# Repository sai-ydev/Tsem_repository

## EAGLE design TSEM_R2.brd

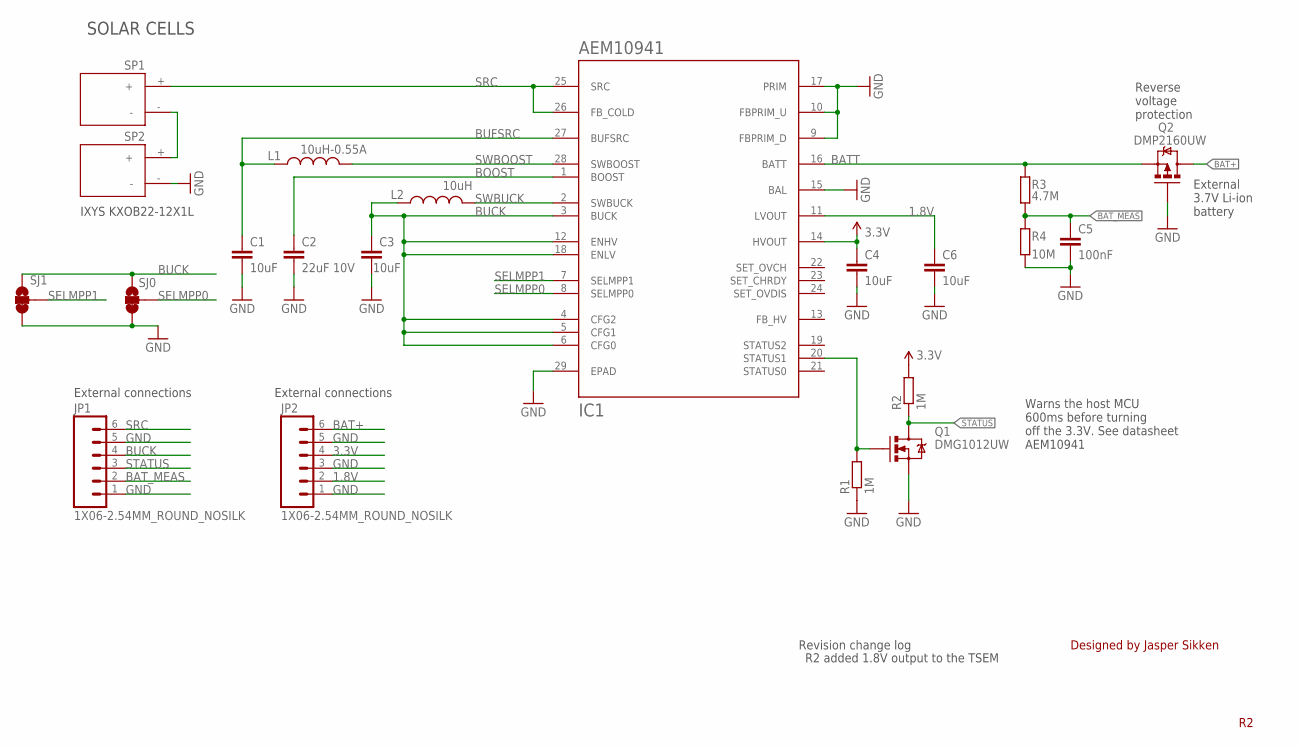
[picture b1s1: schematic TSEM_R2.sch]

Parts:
C1, C3, C4, C6: 10uF; C0603
C2: 22uF 10V; C0603
C5: 100nF; C0402
IC1: AEM10941; QFN50P505X505X90-28
JP1, JP2: 1X06-2.54MM_ROUND_NOSILK; 1X06_2.54MM_ROUND_NOSILK
L1: 10uH-0.55A; LPS4012
L2: 10uH; L0603
Q1: DMG1012UW; SOT323
Q2: DMP2160UW; SOT323
R1, R2: 1M; R0402
R3: 4.7M; R0402
R4: 10M; R0402
SJ0, SJ1: SOLDERJUMPER_3WAY_12SHORT3WAY; SJ_3S_NC_0402
SP1, SP2: KXOB22-12X1; IXYS-KXOB22-12X1

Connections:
1.8V: C6.1, IC1.11 (LVOUT), JP2.2
3.3V: C4.1, IC1.14 (HVOUT), JP2.4, R2.2
BAT+: JP2.6, Q2.3 (D)
BATT: IC1.16 (BATT), Q2.2 (S), R3.2
BAT_MEAS: C5.1, JP1.2, R3.1, R4.2
BOOST: C2.1, IC1.1 (BOOST)
BUCK: C3.1, IC1.3 (BUCK), IC1.4 (CFG2), IC1.5 (CFG1), IC1.6 (CFG0), IC1.12 (ENHV), IC1.18 (ENLV), JP1.4, L2.1, SJ0.3, SJ1.3
BUFSRC: C1.1, IC1.27 (BUFSRC), L1.1
GND: C1.2, C2.2, C3.2, C4.2, C5.2, C6.2, IC1.9 (FBPRIM_D), IC1.10 (FBPRIM_U), IC1.15 (BAL), IC1.17 (PRIM), IC1.29 (EPAD), JP1.1, JP1.5, JP2.1, JP2.3, JP2.5, Q1.2 (S), Q2.1 (G), R1.1, R4.1, SJ0.1, SJ1.1, SP2.-
unnamed: SP1.-, SP2.+
SELMPP0: IC1.8 (SELMPP0), SJ0.2
SELMPP1: IC1.7 (SELMPP1), SJ1.2
SRC: IC1.25 (SRC), IC1.26 (FB_COLD), JP1.6, SP1.+
STATUS: JP1.3, Q1.3 (D), R2.1
STATUS1: IC1.20 (STATUS1), Q1.1 (G), R1.2
SWBOOST: IC1.28 (SWBOOST), L1.2
SWBUCK: IC1.2 (SWBUCK), L2.2

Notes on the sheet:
SOLAR CELLS
IXYS KXOB22-12X1L
Reverse voltage protection
External 3.7V Li-ion battery
Warns the host MCU 600ms before turning off the 3.3V. See datasheet AEM10941
External connections
Designed by Jasper Sikken
Revision change log
R2 added 1.8V output to the TSEM

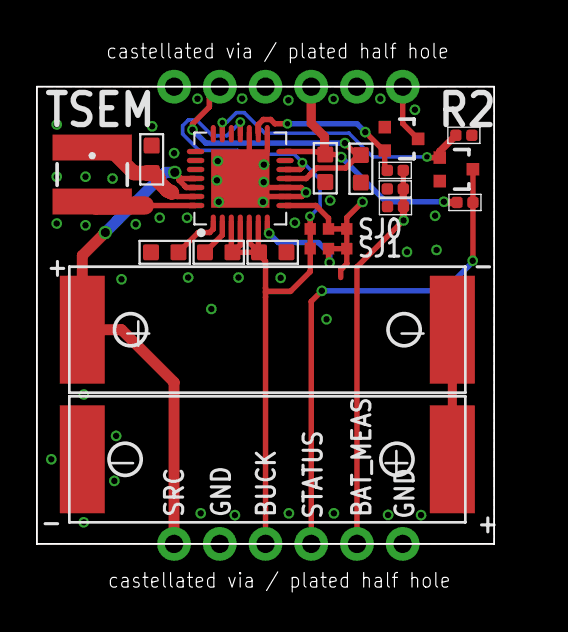
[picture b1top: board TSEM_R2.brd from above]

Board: 2 copper layers, 27.5 x 31.0 mm, 21 parts (0 on the bottom side), 17 nets.

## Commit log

2025-01-02 File download & check-in

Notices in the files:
parts and their libraries:
SparkFun-Aesthetics: Licensing: CC v3.0 Share-Alike You are welcome to use this library for commercial purposes.
